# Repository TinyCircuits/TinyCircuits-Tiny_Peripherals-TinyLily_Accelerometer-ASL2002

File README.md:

# TinyCircuits Tiny Peripherals TinyLily Accelerometer
# ASL1003 Rev1

The design files are located under design_files/ for the TinyCircuits ASL1003 Rev 1 PCB.  This is a Tiny peripheral board that has options for different sensors to be populated.

Format is in Cadsoft Eagle format - Eagle version 6.2 was used for the original design.

For more infomation on this, check out the product page at TinyCircuits.com: https://tinycircuits.com/collections/tinylily/products/tinylily-accelerometer

# License:

Design by TinyCircuits.
All design files are released under the Creative Commons Attribution Share-Alike 3.0 License, see the following link for details: http://creativecommons.org/licenses/by-sa/3.0

All text above must be included in any redistribution or derived design

This project uses designs and concepts developed as part of the Arduino project and the LilyPad project.  The TinyCircuits design files themselves (schematics, PCB and libraries) are not directly derived from these works' design files and have been created new, however the concepts and basic architecture behind the TinyDuino and TinyLily products are derived and we thank the hard work of the organizations below for their contributions to open-source hardware:
  
Original Arduino Uno Design by Team Arduino

LilyPad Arduino Design by Leah Buechley and Sparkfun Electronics

Please support the open-source hardware community

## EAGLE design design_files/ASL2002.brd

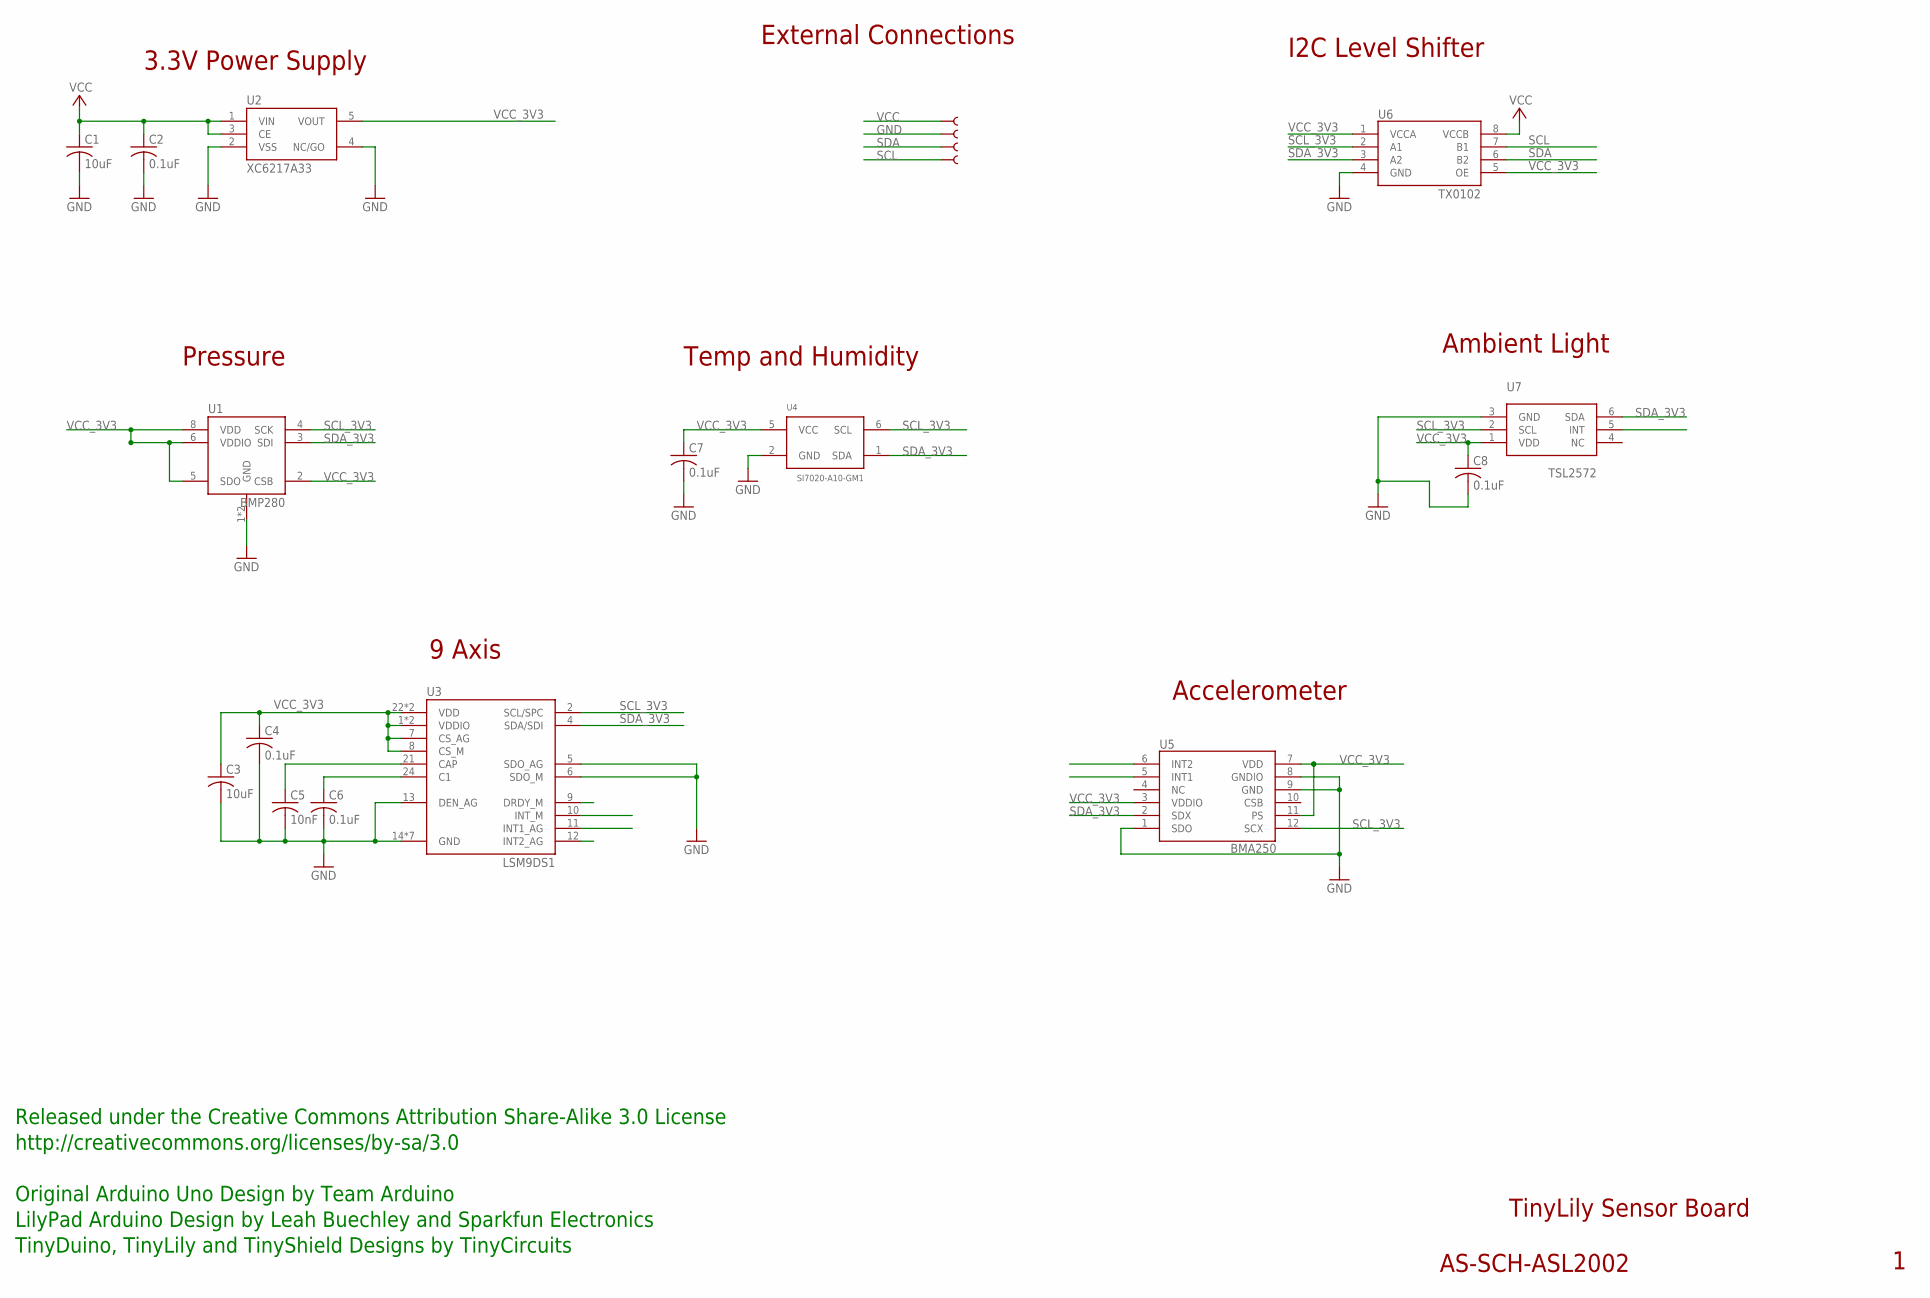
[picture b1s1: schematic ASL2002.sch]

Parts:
$1: SEWTAB; SEWTAP_TH
C1: 10uF; C0603
C2, C4, C7, C8: 0.1uF; C0402; PARTNO AS-ITM-00008
C3: 10uF; C0603; PARTNO AS-ITM-00002
C5: 10nF; C0402
C6: 0.1uF; C0402
U1: BMP280
U2: XC6217A33; SOT-25; PARTNO AS-ITM-00249
U3: LSM9DS1; LGA-24
U4: SI7020-A10-GM1; DFN6
U5: BMA250; 3-AXIS_ACCELEROMETER
U6: TX0102; DQE(R-PX2SON-N8)
U7: TSL2572
U$1, U$2, U$3: SEWTAB; SEWTAP_TH

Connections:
GND: C1.2, C2.2, C3.2, C4.2, C5.2, C6.2, C7.2, C8.2, U1.1 (GND), U1.7 (GND), U2.2 (VSS), U2.4 (NC/GO), U3.5 (SDO_AG), U3.6 (SDO_M), U3.13 (DEN_AG), U3.14 (GND), U3.15 (GND), U3.16 (GND), U3.17 (GND), U3.18 (GND), U3.19 (GND), U3.20 (GND), U4.2 (GND), U5.1 (SDO), U5.8 (GNDIO), U5.9 (GND), U6.4 (GND), U7.3 (GND), U$1.1
unnamed: C5.1, U3.21 (CAP)
unnamed: C6.1, U3.24 (C1)
SCL: U6.7 (B1), U$3.1
SCL_3V3: U1.4 (SCK), U3.2 (SCL/SPC), U4.6 (SCL), U5.12 (SCX), U6.2 (A1), U7.2 (SCL)
SDA: U6.6 (B2), U$2.1
SDA_3V3: U1.3 (SDI), U3.4 (SDA/SDI), U4.1 (SDA), U5.2 (SDX), U6.3 (A2), U7.6 (SDA)
VCC: $1.1, C1.1, C2.1, U2.1 (VIN), U2.3 (CE), U6.8 (VCCB)
VCC_3V3: C3.1, C4.1, C7.1, C8.1, U1.2 (CSB), U1.5 (SDO), U1.6 (VDDIO), U1.8 (VDD), U2.5 (VOUT), U3.1 (VDDIO), U3.3 (VDDIO), U3.7 (CS_AG), U3.8 (CS_M), U3.22 (VDD), U3.23 (VDD), U4.5 (VCC), U5.3 (VDDIO), U5.7 (VDD), U5.11 (PS), U6.1 (VCCA), U6.5 (OE), U7.1 (VDD)

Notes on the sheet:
TinyLily Sensor Board
AS-SCH-ASL2002
Released under the Creative Commons Attribution Share-Alike 3.0 License
http://creativecommons.org/licenses/by-sa/3.0
LilyPad Arduino Design by Leah Buechley and Sparkfun Electronics
TinyDuino, TinyLily and TinyShield Designs by TinyCircuits
Original Arduino Uno Design by Team Arduino
External Connections
3.3V Power Supply
I2C Level Shifter
9 Axis
Pressure
Temp and Humidity
Ambient Light
Accelerometer

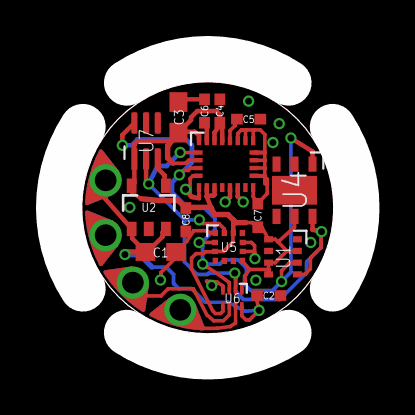
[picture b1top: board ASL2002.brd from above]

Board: 2 copper layers, 14.0 x 14.0 mm, 20 parts (0 on the bottom side), 9 nets.

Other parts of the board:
U$6: DOCFIELD-TINYCIRCUITS-PCB

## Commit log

2019-01-04 update format
2019-05-31 pics
2019-05-31 crop
2019-06-20 images
2020-08-14 transparent bg
2020-08-28 Add CAD data
